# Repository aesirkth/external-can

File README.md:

# External CAN
PCB design and Firmware for an external board that receives and transmits CAN data from the CAN bus.

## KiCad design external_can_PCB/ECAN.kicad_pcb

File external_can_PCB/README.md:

# Potential Component List

* STM32L562CET3P LQFP48 - STM32L5 series processor with 512K Flash, 256K RAM and 48 pins.
* SN65HVD230 - 3.3 V CAN Transceiver with Standby Mode
* JST-XH-4 - CAN side 4-pin connector for CANH, CANL, PWR, GND
* JST-XH-6 - SPI/I2C side 6-pin connector for PWR, GND, SPI_CLK, SPI_SS, SPI_MISO, SPI MOSI
* Possibly SD CARD connector

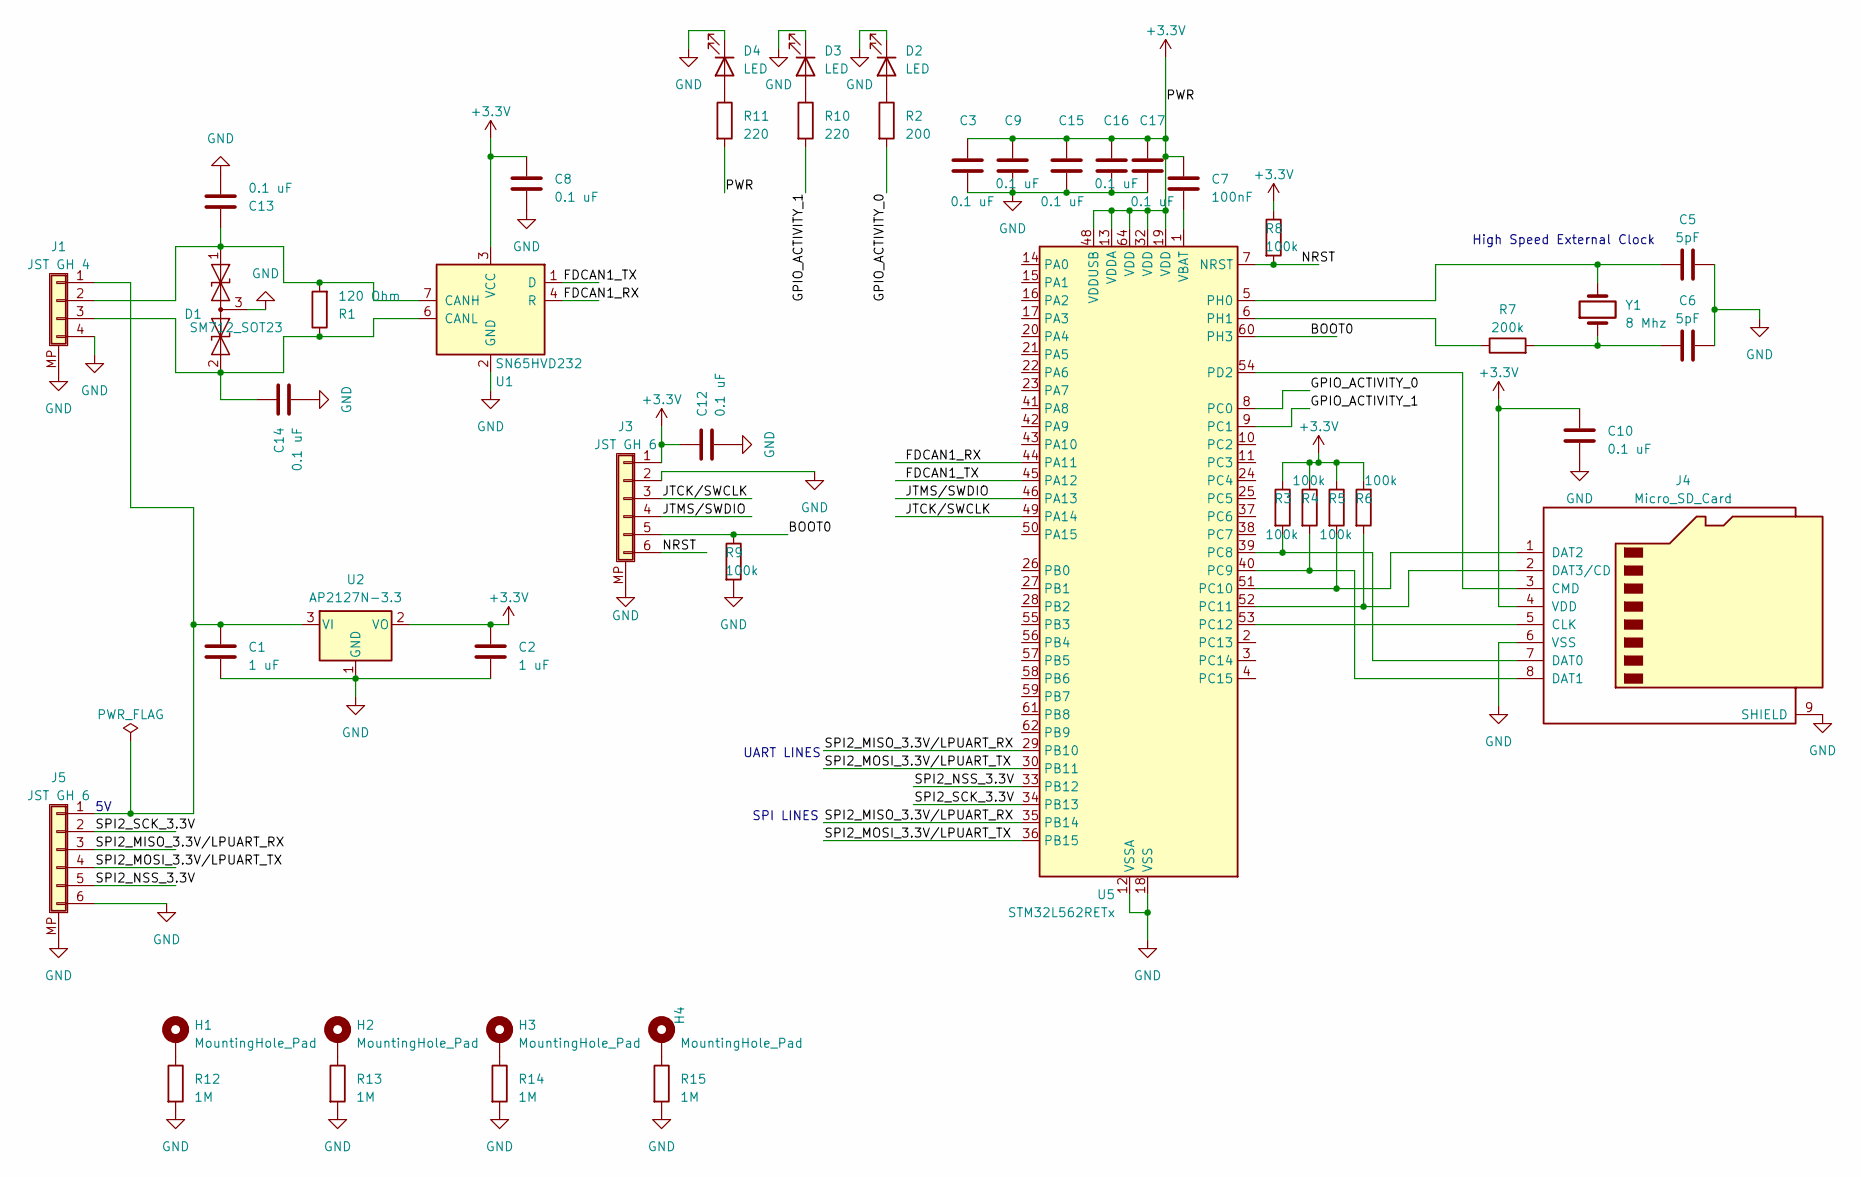
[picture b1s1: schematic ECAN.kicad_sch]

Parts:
C1, C2: 1 uF; C_0402_1005Metric_Pad0.74x0.62mm_HandSolder
C3, C8, C9, C10, C12, C13, C14, C15, C16, C17: 0.1 uF; C_0402_1005Metric_Pad0.74x0.62mm_HandSolder
C5, C6: 5pF; C_0402_1005Metric_Pad0.74x0.62mm_HandSolder
C7: 100nF; C_0402_1005Metric_Pad0.74x0.62mm_HandSolder
D1: SM712_SOT23; SOT-23
D2, D3, D4: LED; LED_0805_2012Metric_Pad1.15x1.40mm_HandSolder
H1, H2, H3, H4: MountingHole_Pad; MountingHole_3.2mm_M3_DIN965_Pad
J1: JST GH 4; JST_GH_SM04B-GHS-TB_1x04-1MP_P1.25mm_Horizontal
J3, J5: JST GH 6; JST_GH_SM06B-GHS-TB_1x06-1MP_P1.25mm_Horizontal
J4: Micro_SD_Card; microSD_HC_Wuerth_693072010801
R1: 120 Ohm; R_0402_1005Metric_Pad0.72x0.64mm_HandSolder
R2: 200; R_0402_1005Metric_Pad0.72x0.64mm_HandSolder
R3, R4, R5, R6, R8, R9: 100k; R_0402_1005Metric_Pad0.72x0.64mm_HandSolder
R7: 200k; R_0402_1005Metric_Pad0.72x0.64mm_HandSolder
R10, R11: 220; R_0402_1005Metric_Pad0.72x0.64mm_HandSolder
R12, R13, R14, R15: 1M; R_0603_1608Metric_Pad0.98x0.95mm_HandSolder
U1: SN65HVD232; SOIC-8_3.9x4.9mm_P1.27mm
U2: AP2127N-3.3; SOT-223-3_TabPin2
U5: STM32L562RETx; LQFP-64_10x10mm_P0.5mm
Y1: 8 Mhz; Crystal_SMD_0603-2Pin_6.0x3.5mm_HandSoldering

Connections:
+3.3V: C2.1, C3.1, C7.2, C8.1, C9.1, C10.1, C12.1, C15.1, C16.1, C17.1, J3.1, J4.4 (VDD), R3.1, R4.1, R5.1, R6.1, R8.1, R11.2, U1.3 (VCC), U2.2 (VO), U5.13 (VDDA), U5.19 (VDD), U5.32 (VDD), U5.48 (VDDUSB), U5.64 (VDD)
/BOOT0: J3.5, R9.1, U5.60 (PH3)
/FDCAN1_RX: U1.4 (R), U5.44 (PA11)
/FDCAN1_TX: U1.1 (D), U5.45 (PA12)
/GPIO_ACTIVITY_0: R2.2, U5.8 (PC0)
/GPIO_ACTIVITY_1: R10.2, U5.9 (PC1)
/JTCK/SWCLK: J3.3, U5.49 (PA14)
/JTMS/SWDIO: J3.4, U5.46 (PA13)
/NRST: J3.6, R8.2, U5.7 (NRST)
/SPI2_MISO_3.3V/LPUART_RX: J5.3, U5.29 (PB10), U5.35 (PB14)
/SPI2_MOSI_3.3V/LPUART_TX: J5.4, U5.30 (PB11), U5.36 (PB15)
/SPI2_NSS_3.3V: J5.5, U5.33 (PB12)
/SPI2_SCK_3.3V: J5.2, U5.34 (PB13)
GND: C1.2, C2.2, C3.2, C5.2, C6.2, C8.2, C9.2, C10.2, C12.2, C13.2, C14.2, C15.2, C16.2, C17.2, D1.3 (common), D2.1 (K), D3.1 (K), D4.1 (K), J1.4, J1.MP (Mount_Point), J3.2, J3.MP (Mount_Point), J4.6 (VSS), J4.9 (SHIELD), J5.6, J5.MP (Mount_Point), R9.2, R12.2, R13.2, R14.2, R15.2, U1.2 (GND), U2.1 (GND), U5.12 (VSSA), U5.18 (VSS), U5.31 (VSS), U5.47 (VSS), U5.63 (VSS)
unnamed: C1.1, J1.1, J5.1, U2.3 (VI)
unnamed: C6.1, R7.2, Y1.1
unnamed: C13.1, D1.1 (A1), J1.2, R1.2, U1.7 (CANH)
unnamed: C14.1, D1.2 (A2), J1.3, R1.1, U1.6 (CANL)
unnamed: D2.2 (A), R2.1
unnamed: D3.2 (A), R10.1
unnamed: D4.2 (A), R11.1
unnamed: H1.1, R12.1
unnamed: H2.1, R13.1
unnamed: H3.1, R14.1
unnamed: H4.1, R15.1
unnamed: J4.5 (CLK), U5.53 (PC12)
unnamed: J4.3 (CMD), U5.54 (PD2)
unnamed: J4.7 (DAT0), R3.2, U5.39 (PC8)
unnamed: J4.8 (DAT1), R4.2, U5.40 (PC9)
unnamed: J4.1 (DAT2), R5.2, U5.51 (PC10)
unnamed: J4.2 (DAT3/CD), R6.2, U5.52 (PC11)
unnamed: C5.1, U5.5 (PH0), Y1.2
unnamed: R7.1, U5.6 (PH1)
unnamed: C7.1, U5.1 (VBAT)

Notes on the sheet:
UART LINES
SPI LINES
High Speed External Clock

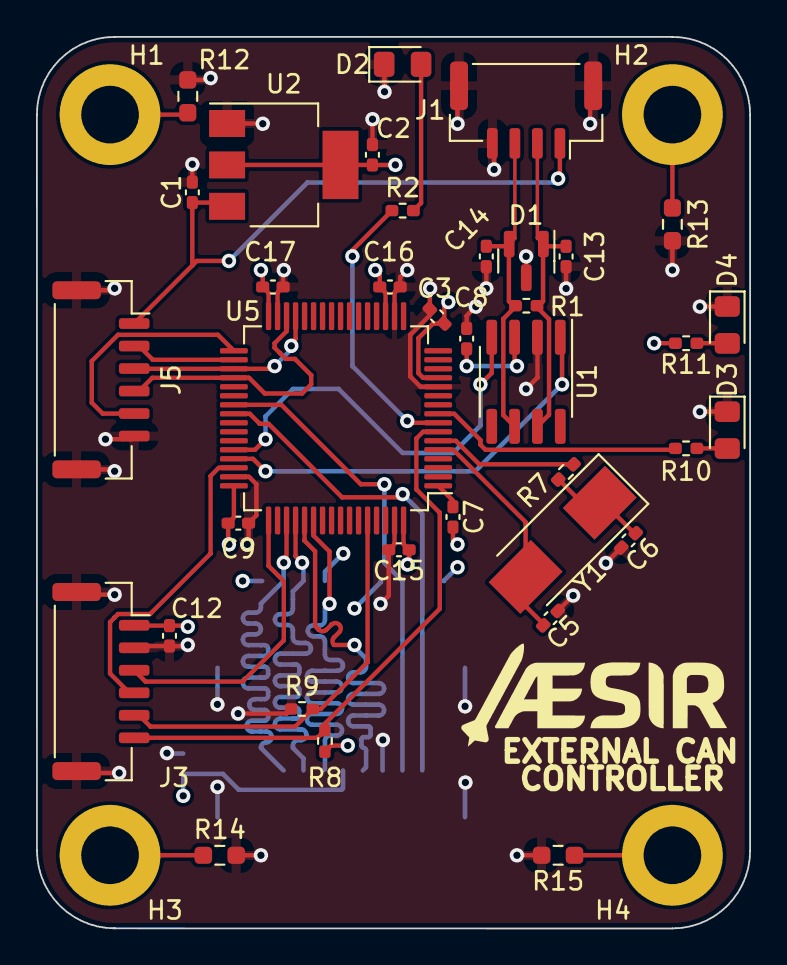
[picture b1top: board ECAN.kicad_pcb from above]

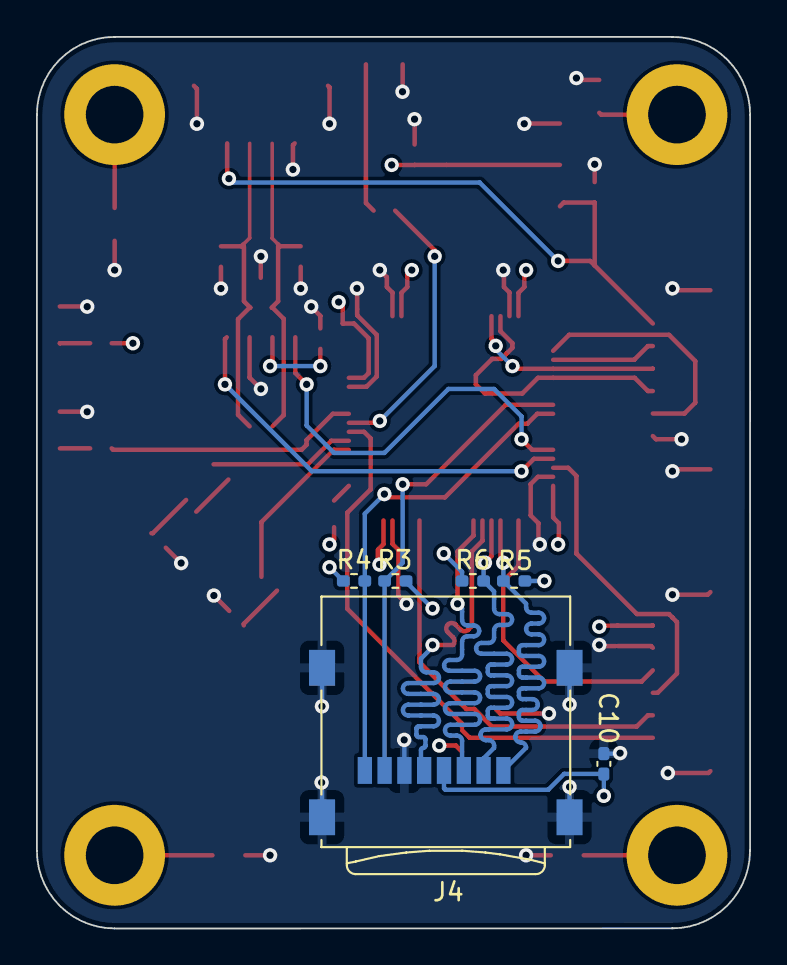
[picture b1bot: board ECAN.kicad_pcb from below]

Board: 4 copper layers, 39.6 x 49.5 mm, 46 parts (6 on the bottom side), 34 nets.

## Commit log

2023-05-04 Main readme
2023-05-04 PCB component README
2023-05-04 Schematic First Version
2023-05-11 Added voltage regulator for 5v->3v3 and Level shifter for SPI 3v3 to 5v
2023-05-23 64 pin package addition (still needs to be connected as pins dont match with 48-pin version)
2023-05-29 64-pin version replacement for stm32
2023-09-18 PCB initial
2023-09-25 Added micro SD Card slot and oscillator
2023-09-26 Added HSE
2023-10-10 PCB layout v1
2023-11-27 Redid ECAN Design: - Removed SPI Level Shifter * Changed JST SH Connector to JST GH * Cleaned up schematic
2023-12-12 Added screw holes and layer pours
2024-02-02 bump
2024-02-06 Addressed issues from Review by Olof
2024-02-13 GPIO LED changes and UART connection to SPI lines
2024-02-13 final length matching
2024-02-13 Bom fix
2024-02-20 Changed CAN connecter reference to 5V, which allows the board to be powered through the CAN connector
2024-02-20 Updated BOM
2024-02-22 ordered version
